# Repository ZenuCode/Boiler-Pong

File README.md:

# Boiler-Pong

Objective
- 2 Player Pong Game with Portal Features that changes the direction/speed of ball when hit.
- Both paddles are able to move in x,y directions within each player's fields.
- Objective is to score the ball into opponent's side and score 5 points to win.

To Play
1. Download src folder
2. Create Project with SystemWorkbench C Project
3. Copy src folder
4. Compile & Run.

Caution for main.c: Easiest to copy the contents of main.c code rather than replacing file.

(SystemWorkbench will need a redirection of path to new main.c file if replaced.)

Components
- STM32(STM32F091RCTx) Microcontroller
- 2x [Adafruit 512 Joystick]
- [2.2" SPI MSP2202 Display]
- TRRS Jack & Speaker

Extra Components
- Custom PCB

Creators
- Paing Khant (pkhant@purdue.edu)
- Henry Oo (henry.hantunoo.2000@gmail.com)
- David Lee (lee2113@purdue.edu)
- Kenny Stier (kenny.stier19@gmail.com)

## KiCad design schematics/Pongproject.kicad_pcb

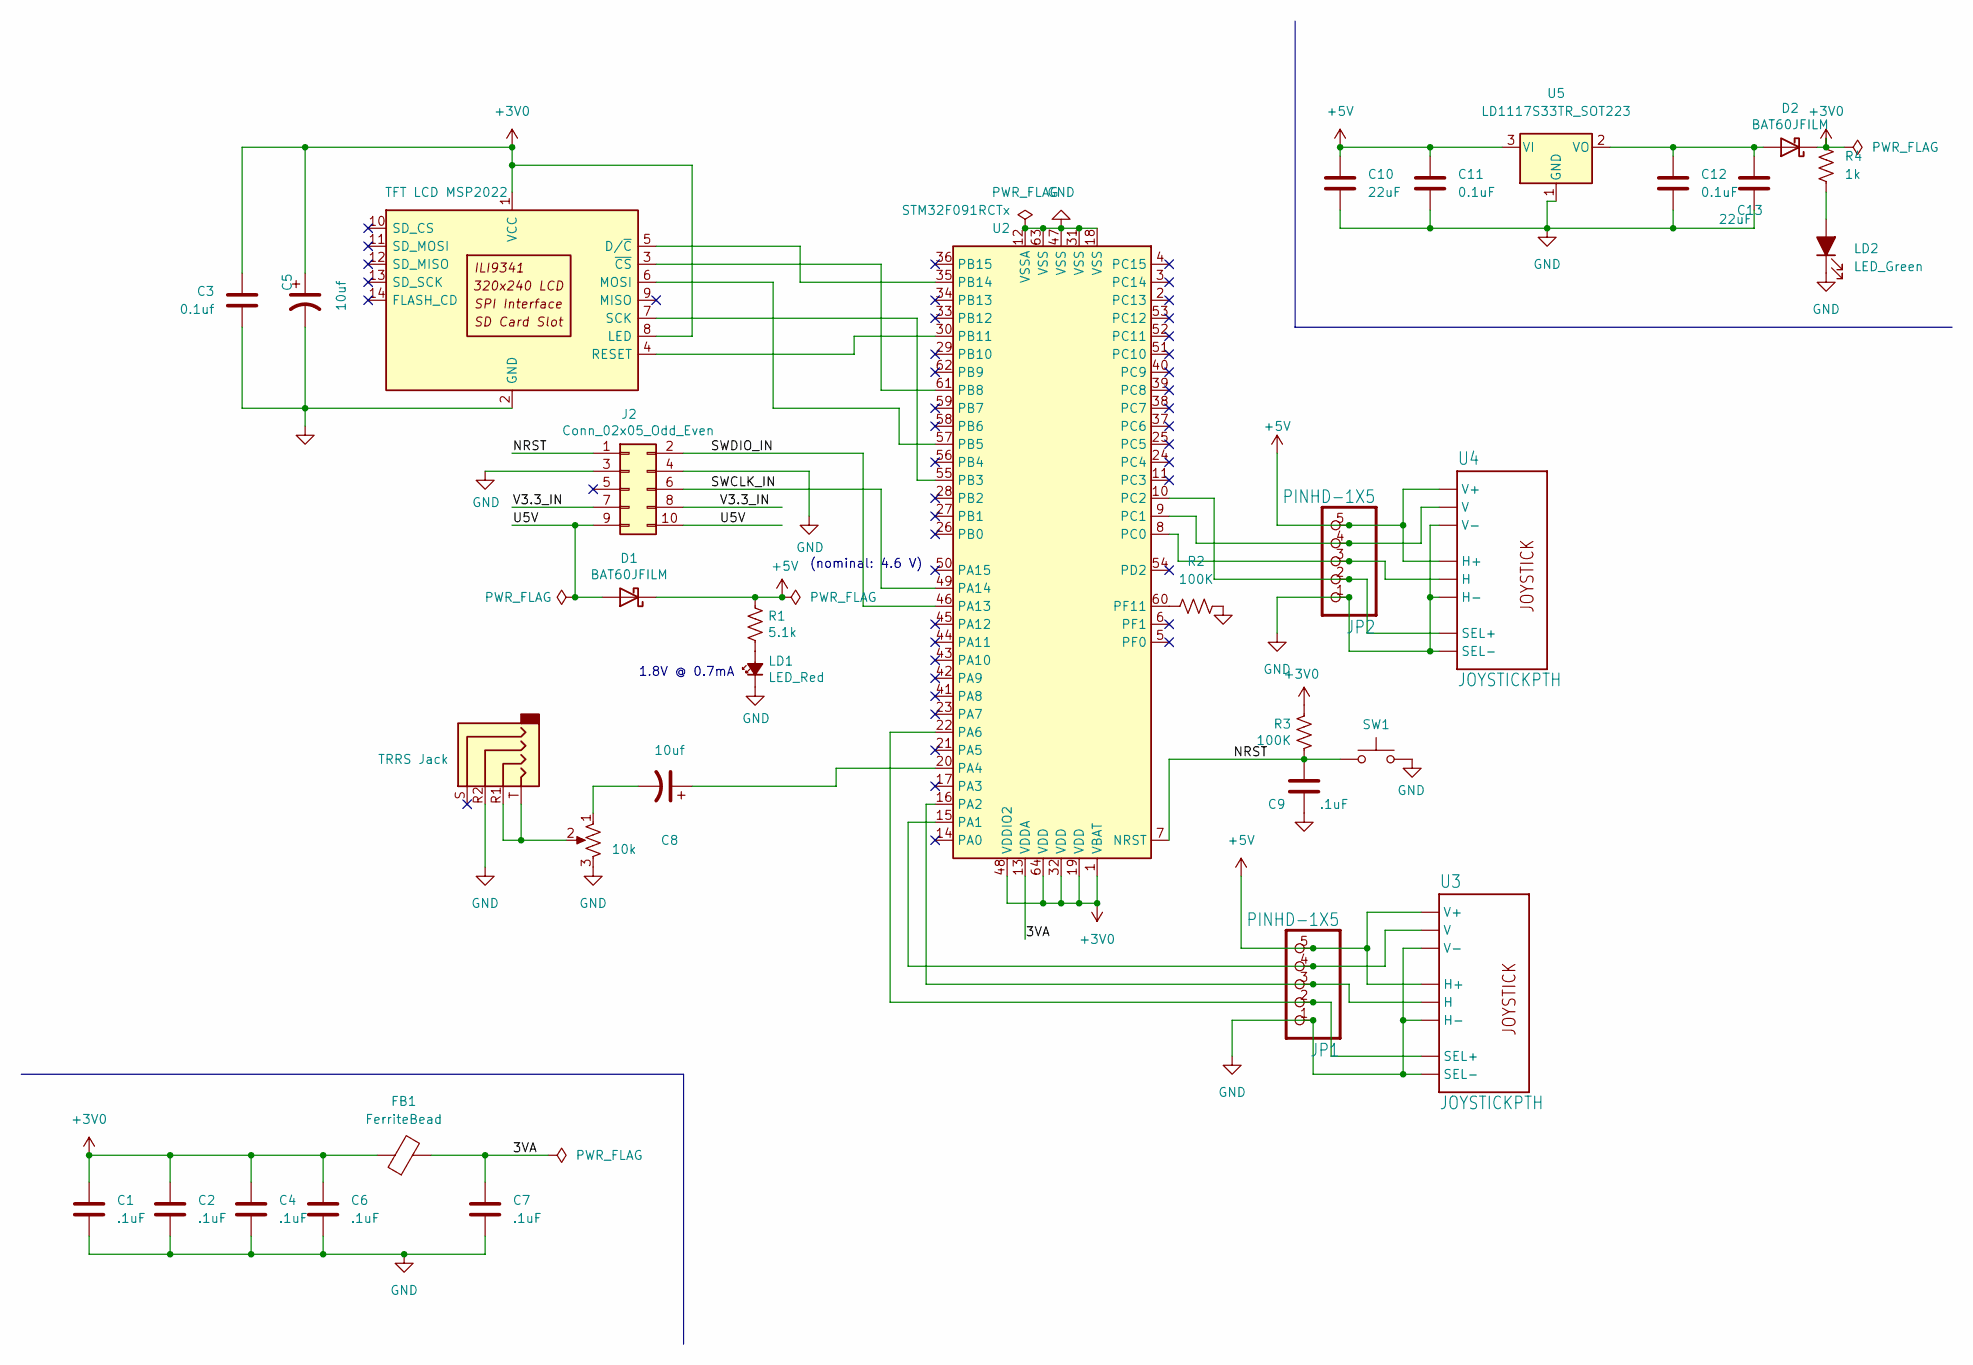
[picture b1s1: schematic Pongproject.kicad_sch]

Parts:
10k1: 10k; Bourns-3310R-0-0-MFG
C1, C2, C4, C6, C7, C9: .1uF; C_0805_2012Metric
C3: 0.1uf; C_0805_2012Metric
C5, C8: 10uf; C_0805_2012Metric
C10, C13: 22uF; C_0805_2012Metric
C11, C12: 0.1uF; C_0805_2012Metric
D1, D2: BAT60JFILM; D_SOD-323
FB1: FerriteBead; L_0805_2012Metric_Pad1.15x1.40mm_HandSolder
J1: TRRS Jack; Jack_3.5mm_PJ320E_Horizontal
J2: Conn_02x05_Odd_Even; IDC-Header_2x05_P2.54mm_Vertical
JP1, JP2: PINHD-1X5; 1X05
LD1: LED_Red; LED_0805_2012Metric
LD2: LED_Green; LED_0805_2012Metric
R1: 5.1k; R_0805_2012Metric
R2, R3: 100K; R_0805_2012Metric
R4: 1k; R_0805_2012Metric
SW1: SW_Push; SW_SPST_PTS645
U1: TFT LCD MSP2022; CR2013-MI2120
U2: STM32F091RCTx; LQFP-64_10x10mm_P0.5mm
U3, U4: JOYSTICKPTH
U5: LD1117S33TR_SOT223; SOT-223-3_TabPin2

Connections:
+3V0: C1.1, C2.1, C3.1, C4.1, C5.1, C6.1, D2.1 (K), FB1.1, R3.1, R4.1, U1.1 (VCC), U1.8 (LED), U2.1 (VBAT), U2.19 (VDD), U2.32 (VDD), U2.48 (VDDIO2), U2.64 (VDD)
+5V: C10.1, C11.1, D1.1 (K), JP1.5, JP2.5, R1.1, U3.H1 (H+), U3.V1 (V+), U4.H1 (H+), U4.V1 (V+), U5.3 (VI)
/3VA: C7.1, FB1.2, U2.13 (VDDA)
/NRST: C9.1, J2.1, R3.2, SW1.2, U2.7 (NRST)
/SWCLK_IN: J2.6, U2.49 (PA14)
/SWDIO_IN: J2.2, U2.46 (PA13)
/U5V: D1.2 (A), J2.9, J2.10
/V3.3_IN: J2.7, J2.8
GND: 10k1.3, C1.2, C2.2, C3.2, C4.2, C5.2, C6.2, C7.2, C9.2, C10.2, C11.2, C12.2, C13.2, J1.R2, J2.3, J2.4, JP1.1, JP2.1, LD1.1 (K), LD2.1 (K), R2.1, SW1.1, U1.2 (GND), U2.12 (VSSA), U2.18 (VSS), U2.31 (VSS), U2.47 (VSS), U2.63 (VSS), U3.B2A (SEL-), U3.H3 (H-), U3.V3 (V-), U4.B2A (SEL-), U4.H3 (H-), U4.V3 (V-), U5.1 (GND)
unnamed: 10k1.1, C8.2
unnamed: 10k1.2, J1.R1, J1.T
unnamed: C8.1, U2.20 (PA4)
unnamed: C12.1, C13.1, D2.2 (A), U5.2 (VO)
unnamed: JP1.2, U2.22 (PA6), U3.B1A (SEL+)
unnamed: JP1.3, U2.16 (PA2), U3.H2 (H)
unnamed: JP1.4, U2.15 (PA1), U3.V2 (V)
unnamed: JP2.2, U2.10 (PC2), U4.B1A (SEL+)
unnamed: JP2.3, U2.8 (PC0), U4.H2 (H)
unnamed: JP2.4, U2.9 (PC1), U4.V2 (V)
unnamed: LD1.2 (A), R1.2
unnamed: LD2.2 (A), R4.2
unnamed: R2.2, U2.60 (PF11)
unnamed: U1.3 (~CS), U2.61 (PB8)
unnamed: U1.4 (RESET), U2.30 (PB11)
unnamed: U1.5 (D/~C), U2.35 (PB14)
unnamed: U1.6 (MOSI), U2.57 (PB5)
unnamed: U1.7 (SCK), U2.55 (PB3)

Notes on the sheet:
(nominal: 4.6 V)
1.8V @ 0.7mA

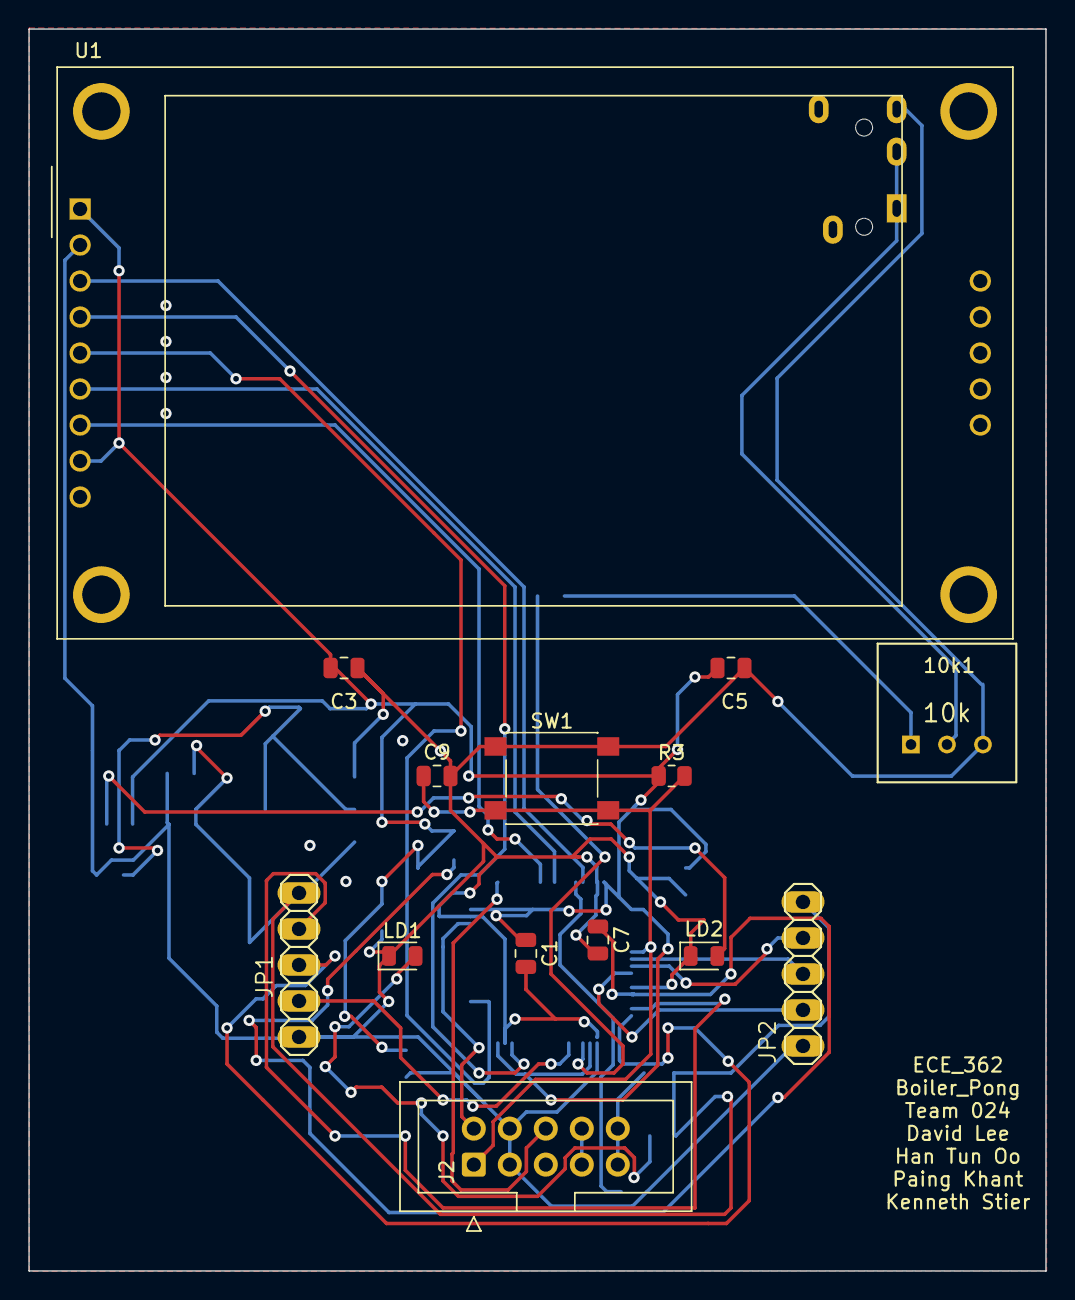
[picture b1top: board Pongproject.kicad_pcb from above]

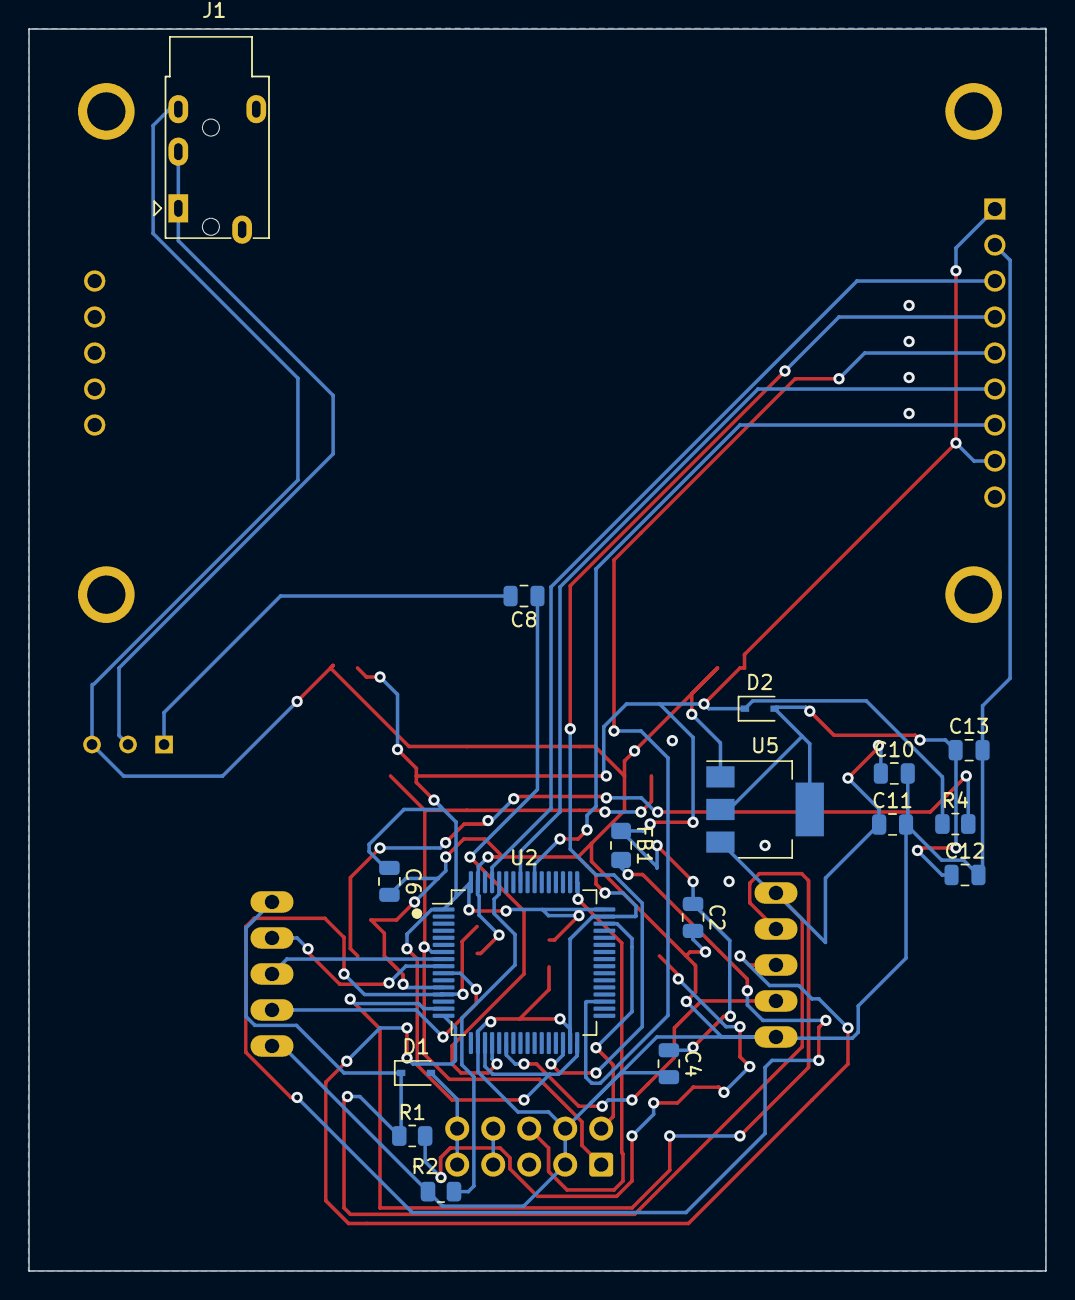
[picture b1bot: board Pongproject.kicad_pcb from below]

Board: 2 copper layers, 71.8 x 87.6 mm, 31 parts (17 on the bottom side), 27 nets.

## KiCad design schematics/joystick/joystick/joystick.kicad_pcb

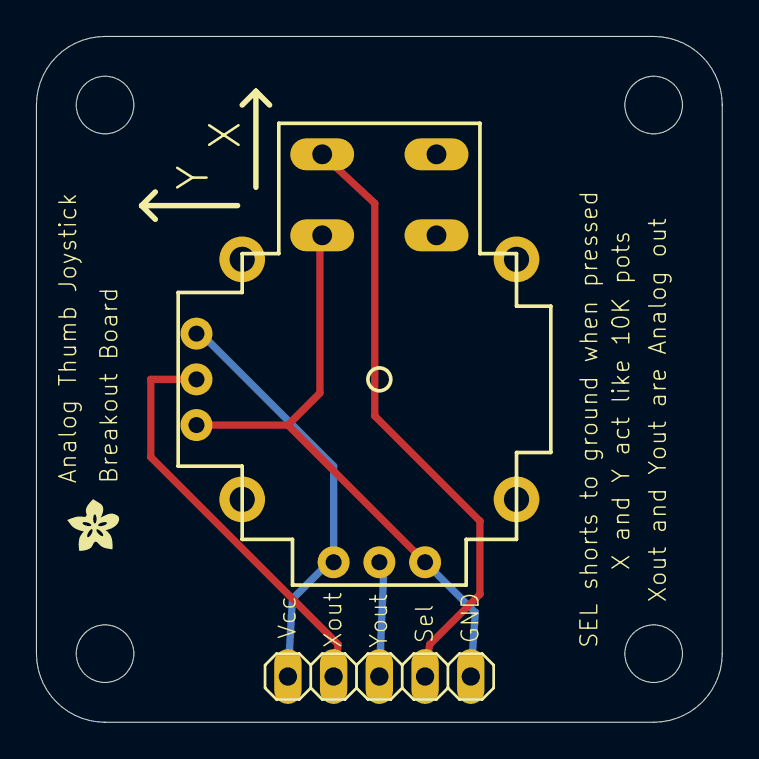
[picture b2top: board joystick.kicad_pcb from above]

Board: 16 copper layers, 38.1 x 38.1 mm, 7 parts (0 on the bottom side), 5 nets.

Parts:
@HOLE0, @HOLE1, @HOLE2, @HOLE3: (no value)
JP1: 1X05
U1: JOYSTICKPTH; JOYSTICK
U$1: ADAFRUIT200MIL

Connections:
unnamed: JP1.5, U1.H1, U1.V1
unnamed: JP1.1, U1.B2A, U1.H3, U1.V3
unnamed: JP1.4, U1.V2
unnamed: JP1.3, U1.H2
unnamed: JP1.2, U1.B1A

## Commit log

2022-06-03 Final
